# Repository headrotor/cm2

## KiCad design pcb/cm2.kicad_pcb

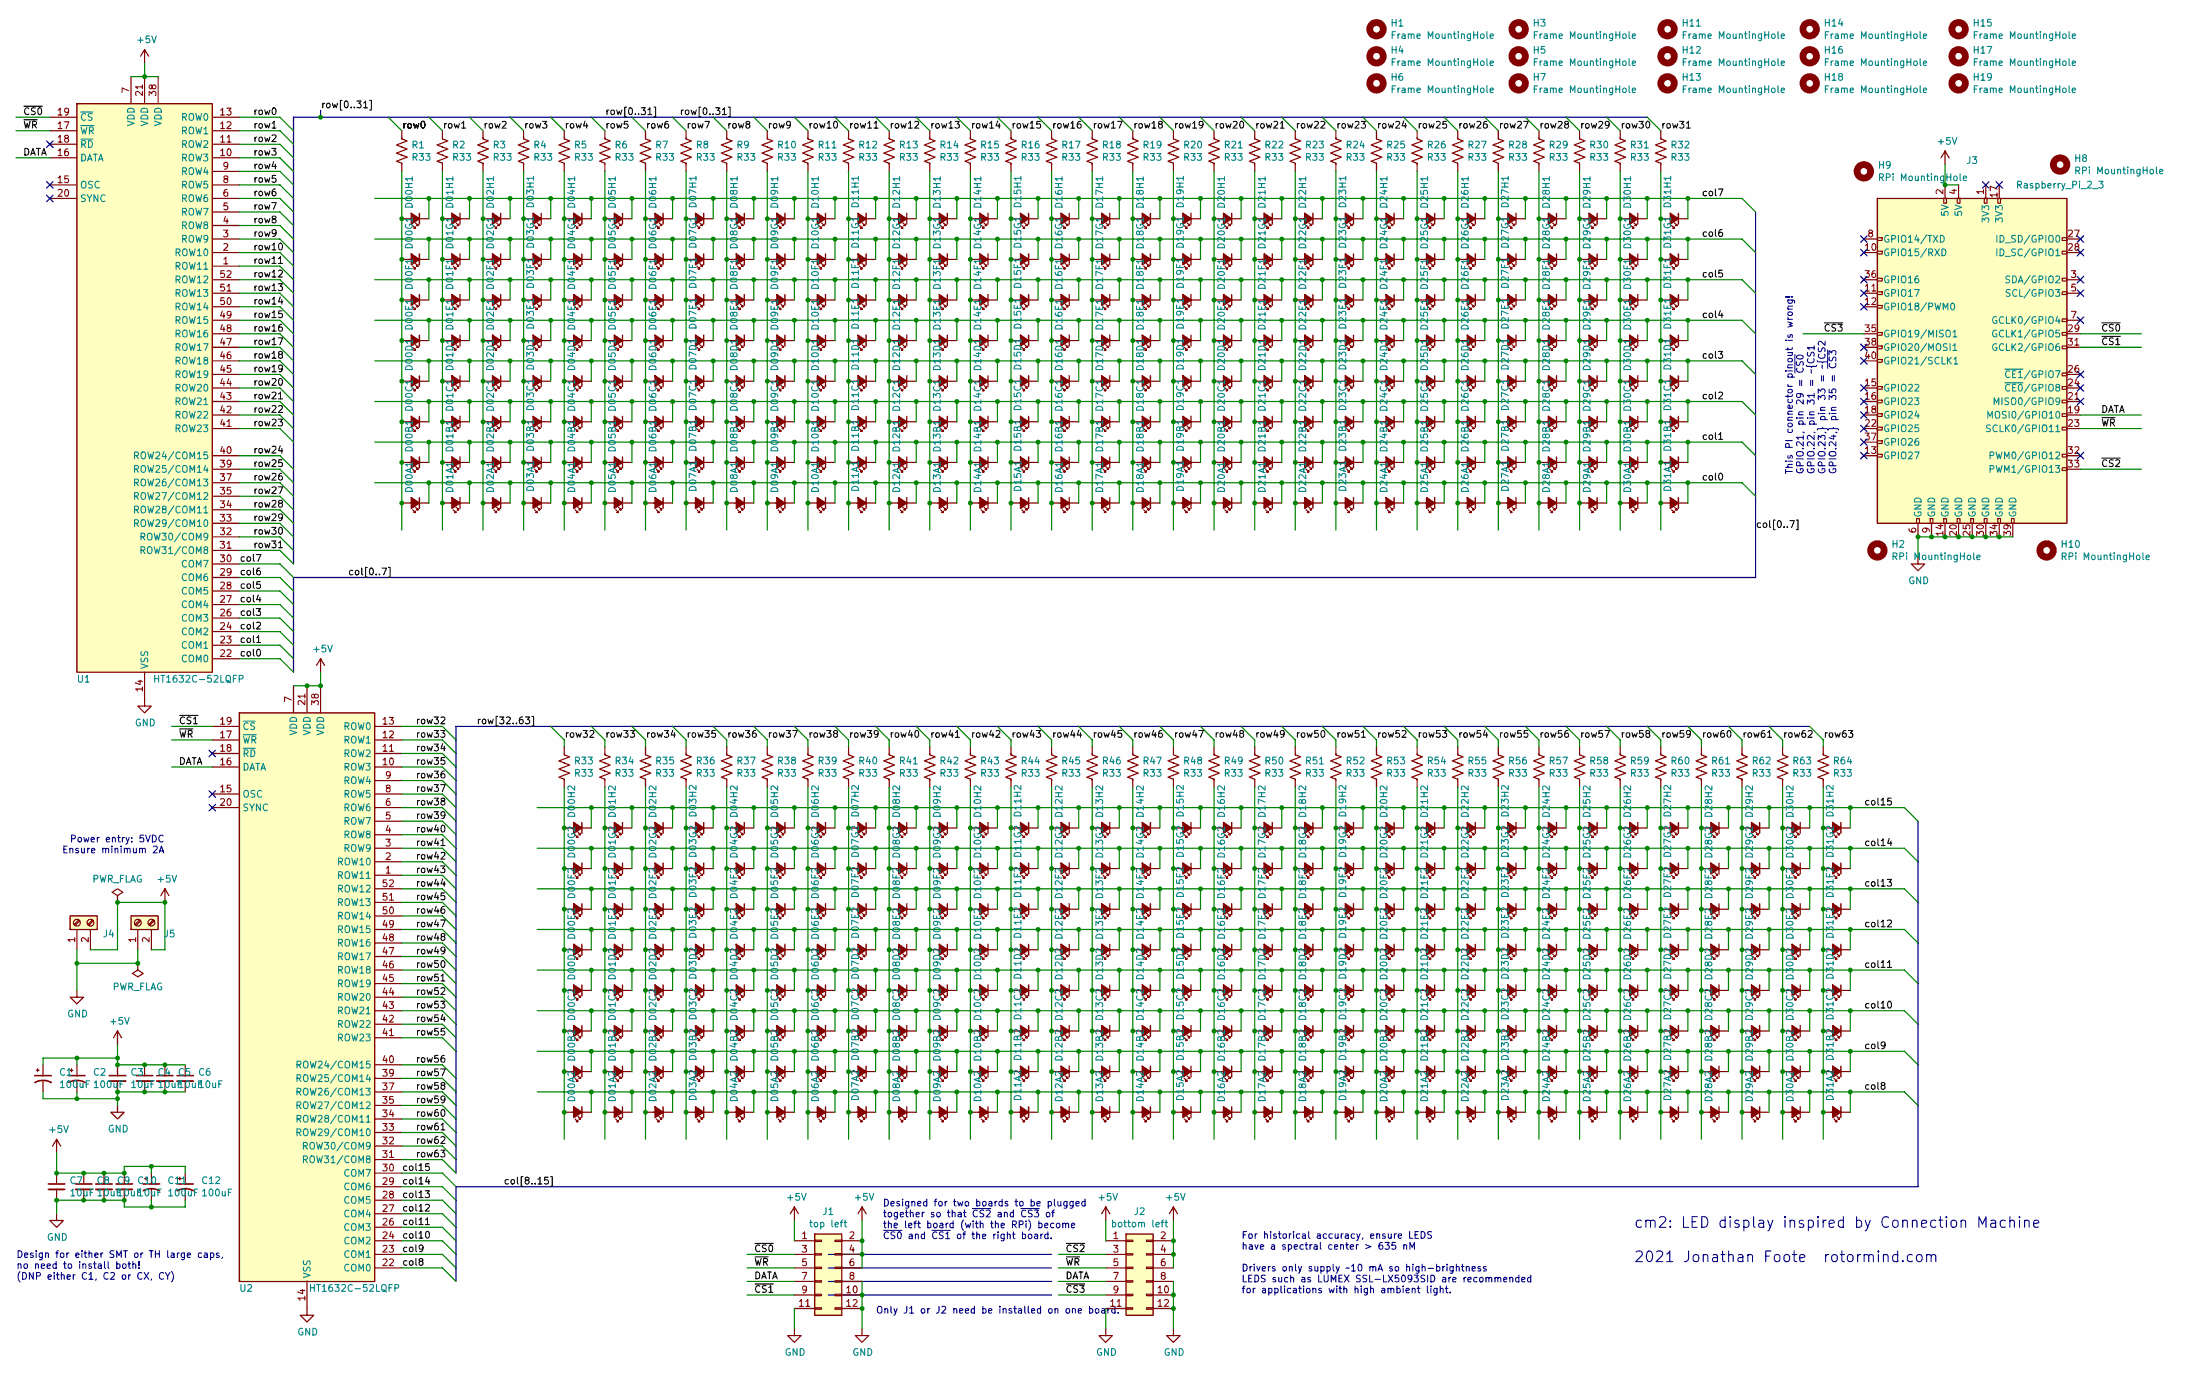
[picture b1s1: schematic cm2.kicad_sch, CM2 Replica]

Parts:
C1, C2: 100uF; CP_Radial_D6.3mm_P2.50mm
C3, C4, C5, C6, C7, C8, C9, C10: 10uF; C_1206_3216Metric_Pad1.33x1.80mm_HandSolder
C11, C12: 100uF; CP_Elec_6.3x7.7
D00A1, D00A2, D00B1, D00B2, D00C1, D00C2, D00D1, D00D2, D00E1, D00E2, D00F1, D00F2, D00G1, D00G2, D00H1, D00H2, D01A1, D01A2, D01B1, D01B2, D01C1, D01C2, D01D1, D01D2, D01E1, D01E2, D01F1, D01F2, D01G1, D01G2, D01H1, D01H2, D02A1, D02A2, D02B1, D02B2, D02C1, D02C2, D02D1, D02D2, D02E1, D02E2, D02F1, D02F2, D02G1, D02G2, D02H1, D02H2, D03A1, D03A2, D03B1, D03B2, D03C1, D03C2, D03D1, D03D2, D03E1, D03E2, D03F1, D03F2, D03G1, D03G2, D03H1, D03H2, D04A1, D04A2, D04B1, D04B2, D04C1, D04C2, D04D1, D04D2, D04E1, D04E2, D04F1, D04F2, D04G1, D04G2, D04H1, D04H2, D05A1, D05A2, D05B1, D05B2, D05C1, D05C2, D05D1, D05D2, D05E1, D05E2, D05F1, D05F2, D05G1, D05G2, D05H1, D05H2, D06A1, D06A2, D06B1, D06B2, D06C1, D06C2, D06D1, D06D2, D06E1, D06E2, D06F1, D06F2, D06G1, D06G2, D06H1, D06H2, D07A1, D07A2, D07B1, D07B2, D07C1, D07C2, D07D1, D07D2, D07E1, D07E2, D07F1, D07F2, D07G1, D07G2, D07H1, D07H2, D08A1, D08A2, D08B1, D08B2, D08C1, D08C2, D08D1, D08D2, D08E1, D08E2, D08F1, D08F2, D08G1, D08G2, D08H1, D08H2, D09A1, D09A2, D09B1, D09B2, D09C1, D09C2, D09D1, D09D2, D09E1, D09E2, D09F1, D09F2, D09G1, D09G2, D09H1, D09H2, D10A1, D10A2, D10B1, D10B2, D10C1, D10C2, D10D1, D10D2, D10E1, D10E2, D10F1, D10F2, D10G1, D10G2, D10H1, D10H2, D11A1, D11A2, D11B1, D11B2, D11C1, D11C2, D11D1, D11D2, D11E1, D11E2, D11F1, D11F2, D11G1, D11G2, D11H1, D11H2, D12A1, D12A2, D12B1, D12B2, D12C1, D12C2, D12D1, D12D2, D12E1, D12E2, D12F1, D12F2, D12G1, D12G2, D12H1, D12H2, D13A1, D13A2, D13B1, D13B2, D13C1, D13C2, D13D1, D13D2, D13E1, D13E2, D13F1, D13F2, D13G1, D13G2, D13H1, D13H2, D14A1, D14A2, D14B1, D14B2, D14C1, D14C2, D14D1, D14D2, D14E1, D14E2, D14F1, D14F2, D14G1, D14G2, D14H1, D14H2, D15A1, D15A2, D15B1, D15B2, D15C1, D15C2, D15D1, D15D2, D15E1, D15E2, D15F1, D15F2, D15G1, D15G2, D15H1, D15H2, D16A1, D16A2, D16B1, D16B2, D16C1, D16C2, D16D1, D16D2, D16E1, D16E2, D16F1, D16F2, D16G1, D16G2, D16H1, D16H2, D17A1, D17A2, D17B1, D17B2, D17C1, D17C2, D17D1, D17D2, D17E1, D17E2, D17F1, D17F2, D17G1, D17G2, D17H1, D17H2, D18A1, D18A2, D18B1, D18B2, D18C1, D18C2, D18D1, D18D2, D18E1, D18E2, D18F1, D18F2, D18G1, D18G2, D18H1, D18H2, D19A1, D19A2, D19B1, D19B2, D19C1, D19C2, D19D1, D19D2, D19E1, D19E2, D19F1, D19F2, D19G1, D19G2, D19H1, D19H2, D20A1, D20A2, D20B1, D20B2, D20C1, D20C2, D20D1, D20D2, D20E1, D20E2, D20F1, D20F2, D20G1, D20G2, D20H1, D20H2, D21A1, D21A2, D21B1, D21B2, D21C1, D21C2, D21D1, D21D2, D21E1, D21E2, D21F1, D21F2, D21G1, D21G2, D21H1, D21H2, D22A1, D22A2, D22B1, D22B2, D22C1, D22C2, D22D1, D22D2, D22E1, D22E2, D22F1, D22F2, D22G1, D22G2, D22H1, D22H2, D23A1, D23A2, D23B1, D23B2, D23C1, D23C2, D23D1, D23D2, D23E1, D23E2, D23F1, D23F2, D23G1, D23G2, D23H1, D23H2, D24A1, D24A2, D24B1, D24B2, D24C1, D24C2, D24D1, D24D2, D24E1, D24E2, D24F1, D24F2, D24G1, D24G2, D24H1, D24H2, D25A1, D25A2, D25B1, D25B2, D25C1, D25C2, D25D1, D25D2, D25E1, D25E2, D25F1, D25F2, D25G1, D25G2, D25H1, D25H2, D26A1, D26A2, D26B1, D26B2, D26C1, D26C2, D26D1, D26D2, D26E1, D26E2, D26F1, D26F2, D26G1, D26G2, D26H1, D26H2, D27A1, D27A2, D27B1, D27B2, D27C1, D27C2, D27D1, D27D2, D27E1, D27E2, D27F1, D27F2, D27G1, D27G2, D27H1, D27H2, D28A1, D28A2, D28B1, D28B2, D28C1, D28C2, D28D1, D28D2, D28E1, D28E2, D28F1, D28F2, D28G1, D28G2, D28H1, D28H2, D29A1, D29A2, D29B1, D29B2, D29C1, D29C2, D29D1, D29D2, D29E1, D29E2, D29F1, D29F2, D29G1, D29G2, D29H1, D29H2, D30A1, D30A2, D30B1, D30B2, D30C1, D30C2, D30D1, D30D2, D30E1, D30E2, D30F1, D30F2, D30G1, D30G2, D30H1, D30H2, D31A1, D31A2, D31B1, D31B2, D31C1, D31C2, D31D1, D31D2, D31E1, D31E2, D31F1, D31F2, D31G1, D31G2, D31H1, D31H2: LED_Small_ALT; LED_D5.0mm
H1, H3, H4, H5, H6, H7, H11, H12, H13, H14, H15, H16, H17, H18, H19: Frame MountingHole; MountingHole_3.2mm_M3
H2, H8, H9, H10: RPi MountingHole; MountingHole_2.5mm
J1: top left; PinHeader_2x06_P2.54mm_Horizontal
J2: bottom left; PinSocket_2x06_P2.54mm_Horizontal
J3: Raspberry_Pi_2_3; PinSocket_2x20_P2.54mm_Vertical
J4, J5: Screw_Terminal_01x02; TerminalBlock_bornier-2_P5.08mm
R1, R2, R3, R4, R5, R6, R7, R8, R9, R10, R11, R12, R13, R14, R15, R16, R17, R18, R19, R20, R21, R22, R23, R24, R25, R26, R27, R28, R29, R30, R31, R32, R33, R34, R35, R36, R37, R38, R39, R40, R41, R42, R43, R44, R45, R46, R47, R48, R49, R50, R51, R52, R53, R54, R55, R56, R57, R58, R59, R60, R61, R62, R63, R64: R33; R_0603_1608Metric_Pad0.98x0.95mm_HandSolder
U1, U2: HT1632C-52LQFP; LQFP-52_14x14mm_P1mm

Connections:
+5V: C1.1, C2.1, C3.1, C4.1, C5.1, C6.1, C7.1, C8.1, C9.1, C10.1, C11.1, C12.1, J1.1, J1.2, J1.4, J1.6, J2.1, J2.2, J2.4, J2.6, J3.2 (5V), J3.4 (5V), J4.2, J5.2, U1.7 (VDD), U1.21 (VDD), U1.38 (VDD), U2.7 (VDD), U2.21 (VDD), U2.38 (VDD); also elsewhere on the board
/DATA: J1.7, J2.7, J3.19 (MOSI0/GPIO10), U1.16 (DATA), U2.16 (DATA)
/col0: D00A1.1 (K), D01A1.1 (K), D02A1.1 (K), D03A1.1 (K), D04A1.1 (K), D05A1.1 (K), D06A1.1 (K), D07A1.1 (K), D08A1.1 (K), D09A1.1 (K), D10A1.1 (K), D11A1.1 (K), D12A1.1 (K), D13A1.1 (K), D14A1.1 (K), D15A1.1 (K), D16A1.1 (K), D17A1.1 (K), D18A1.1 (K), D19A1.1 (K), D20A1.1 (K), D21A1.1 (K), D22A1.1 (K), D23A1.1 (K), D24A1.1 (K), D25A1.1 (K), D26A1.1 (K), D27A1.1 (K), D28A1.1 (K), D29A1.1 (K), D30A1.1 (K), D31A1.1 (K), U1.22 (COM0)
/col1: D00B1.1 (K), D01B1.1 (K), D02B1.1 (K), D03B1.1 (K), D04B1.1 (K), D05B1.1 (K), D06B1.1 (K), D07B1.1 (K), D08B1.1 (K), D09B1.1 (K), D10B1.1 (K), D11B1.1 (K), D12B1.1 (K), D13B1.1 (K), D14B1.1 (K), D15B1.1 (K), D16B1.1 (K), D17B1.1 (K), D18B1.1 (K), D19B1.1 (K), D20B1.1 (K), D21B1.1 (K), D22B1.1 (K), D23B1.1 (K), D24B1.1 (K), D25B1.1 (K), D26B1.1 (K), D27B1.1 (K), D28B1.1 (K), D29B1.1 (K), D30B1.1 (K), D31B1.1 (K), U1.23 (COM1)
/col2: D00C1.1 (K), D01C1.1 (K), D02C1.1 (K), D03C1.1 (K), D04C1.1 (K), D05C1.1 (K), D06C1.1 (K), D07C1.1 (K), D08C1.1 (K), D09C1.1 (K), D10C1.1 (K), D11C1.1 (K), D12C1.1 (K), D13C1.1 (K), D14C1.1 (K), D15C1.1 (K), D16C1.1 (K), D17C1.1 (K), D18C1.1 (K), D19C1.1 (K), D20C1.1 (K), D21C1.1 (K), D22C1.1 (K), D23C1.1 (K), D24C1.1 (K), D25C1.1 (K), D26C1.1 (K), D27C1.1 (K), D28C1.1 (K), D29C1.1 (K), D30C1.1 (K), D31C1.1 (K), U1.24 (COM2)
/col3: D00D1.1 (K), D01D1.1 (K), D02D1.1 (K), D03D1.1 (K), D04D1.1 (K), D05D1.1 (K), D06D1.1 (K), D07D1.1 (K), D08D1.1 (K), D09D1.1 (K), D10D1.1 (K), D11D1.1 (K), D12D1.1 (K), D13D1.1 (K), D14D1.1 (K), D15D1.1 (K), D16D1.1 (K), D17D1.1 (K), D18D1.1 (K), D19D1.1 (K), D20D1.1 (K), D21D1.1 (K), D22D1.1 (K), D23D1.1 (K), D24D1.1 (K), D25D1.1 (K), D26D1.1 (K), D27D1.1 (K), D28D1.1 (K), D29D1.1 (K), D30D1.1 (K), D31D1.1 (K), U1.26 (COM3)
/col4: D00E1.1 (K), D01E1.1 (K), D02E1.1 (K), D03E1.1 (K), D04E1.1 (K), D05E1.1 (K), D06E1.1 (K), D07E1.1 (K), D08E1.1 (K), D09E1.1 (K), D10E1.1 (K), D11E1.1 (K), D12E1.1 (K), D13E1.1 (K), D14E1.1 (K), D15E1.1 (K), D16E1.1 (K), D17E1.1 (K), D18E1.1 (K), D19E1.1 (K), D20E1.1 (K), D21E1.1 (K), D22E1.1 (K), D23E1.1 (K), D24E1.1 (K), D25E1.1 (K), D26E1.1 (K), D27E1.1 (K), D28E1.1 (K), D29E1.1 (K), D30E1.1 (K), D31E1.1 (K), U1.27 (COM4)
/col5: D00F1.1 (K), D01F1.1 (K), D02F1.1 (K), D03F1.1 (K), D04F1.1 (K), D05F1.1 (K), D06F1.1 (K), D07F1.1 (K), D08F1.1 (K), D09F1.1 (K), D10F1.1 (K), D11F1.1 (K), D12F1.1 (K), D13F1.1 (K), D14F1.1 (K), D15F1.1 (K), D16F1.1 (K), D17F1.1 (K), D18F1.1 (K), D19F1.1 (K), D20F1.1 (K), D21F1.1 (K), D22F1.1 (K), D23F1.1 (K), D24F1.1 (K), D25F1.1 (K), D26F1.1 (K), D27F1.1 (K), D28F1.1 (K), D29F1.1 (K), D30F1.1 (K), D31F1.1 (K), U1.28 (COM5)
/col6: D00G1.1 (K), D01G1.1 (K), D02G1.1 (K), D03G1.1 (K), D04G1.1 (K), D05G1.1 (K), D06G1.1 (K), D07G1.1 (K), D08G1.1 (K), D09G1.1 (K), D10G1.1 (K), D11G1.1 (K), D12G1.1 (K), D13G1.1 (K), D14G1.1 (K), D15G1.1 (K), D16G1.1 (K), D17G1.1 (K), D18G1.1 (K), D19G1.1 (K), D20G1.1 (K), D21G1.1 (K), D22G1.1 (K), D23G1.1 (K), D24G1.1 (K), D25G1.1 (K), D26G1.1 (K), D27G1.1 (K), D28G1.1 (K), D29G1.1 (K), D30G1.1 (K), D31G1.1 (K), U1.29 (COM6)
/col7: D00H1.1 (K), D01H1.1 (K), D02H1.1 (K), D03H1.1 (K), D04H1.1 (K), D05H1.1 (K), D06H1.1 (K), D07H1.1 (K), D08H1.1 (K), D09H1.1 (K), D10H1.1 (K), D11H1.1 (K), D12H1.1 (K), D13H1.1 (K), D14H1.1 (K), D15H1.1 (K), D16H1.1 (K), D17H1.1 (K), D18H1.1 (K), D19H1.1 (K), D20H1.1 (K), D21H1.1 (K), D22H1.1 (K), D23H1.1 (K), D24H1.1 (K), D25H1.1 (K), D26H1.1 (K), D27H1.1 (K), D28H1.1 (K), D29H1.1 (K), D30H1.1 (K), D31H1.1 (K), U1.30 (COM7)
/col8: D00A2.1 (K), D01A2.1 (K), D02A2.1 (K), D03A2.1 (K), D04A2.1 (K), D05A2.1 (K), D06A2.1 (K), D07A2.1 (K), D08A2.1 (K), D09A2.1 (K), D10A2.1 (K), D11A2.1 (K), D12A2.1 (K), D13A2.1 (K), D14A2.1 (K), D15A2.1 (K), D16A2.1 (K), D17A2.1 (K), D18A2.1 (K), D19A2.1 (K), D20A2.1 (K), D21A2.1 (K), D22A2.1 (K), D23A2.1 (K), D24A2.1 (K), D25A2.1 (K), D26A2.1 (K), D27A2.1 (K), D28A2.1 (K), D29A2.1 (K), D30A2.1 (K), D31A2.1 (K), U2.22 (COM0)
/col9: D00B2.1 (K), D01B2.1 (K), D02B2.1 (K), D03B2.1 (K), D04B2.1 (K), D05B2.1 (K), D06B2.1 (K), D07B2.1 (K), D08B2.1 (K), D09B2.1 (K), D10B2.1 (K), D11B2.1 (K), D12B2.1 (K), D13B2.1 (K), D14B2.1 (K), D15B2.1 (K), D16B2.1 (K), D17B2.1 (K), D18B2.1 (K), D19B2.1 (K), D20B2.1 (K), D21B2.1 (K), D22B2.1 (K), D23B2.1 (K), D24B2.1 (K), D25B2.1 (K), D26B2.1 (K), D27B2.1 (K), D28B2.1 (K), D29B2.1 (K), D30B2.1 (K), D31B2.1 (K), U2.23 (COM1)
/col10: D00C2.1 (K), D01C2.1 (K), D02C2.1 (K), D03C2.1 (K), D04C2.1 (K), D05C2.1 (K), D06C2.1 (K), D07C2.1 (K), D08C2.1 (K), D09C2.1 (K), D10C2.1 (K), D11C2.1 (K), D12C2.1 (K), D13C2.1 (K), D14C2.1 (K), D15C2.1 (K), D16C2.1 (K), D17C2.1 (K), D18C2.1 (K), D19C2.1 (K), D20C2.1 (K), D21C2.1 (K), D22C2.1 (K), D23C2.1 (K), D24C2.1 (K), D25C2.1 (K), D26C2.1 (K), D27C2.1 (K), D28C2.1 (K), D29C2.1 (K), D30C2.1 (K), D31C2.1 (K), U2.24 (COM2)
/col11: D00D2.1 (K), D01D2.1 (K), D02D2.1 (K), D03D2.1 (K), D04D2.1 (K), D05D2.1 (K), D06D2.1 (K), D07D2.1 (K), D08D2.1 (K), D09D2.1 (K), D10D2.1 (K), D11D2.1 (K), D12D2.1 (K), D13D2.1 (K), D14D2.1 (K), D15D2.1 (K), D16D2.1 (K), D17D2.1 (K), D18D2.1 (K), D19D2.1 (K), D20D2.1 (K), D21D2.1 (K), D22D2.1 (K), D23D2.1 (K), D24D2.1 (K), D25D2.1 (K), D26D2.1 (K), D27D2.1 (K), D28D2.1 (K), D29D2.1 (K), D30D2.1 (K), D31D2.1 (K), U2.26 (COM3)
/col12: D00E2.1 (K), D01E2.1 (K), D02E2.1 (K), D03E2.1 (K), D04E2.1 (K), D05E2.1 (K), D06E2.1 (K), D07E2.1 (K), D08E2.1 (K), D09E2.1 (K), D10E2.1 (K), D11E2.1 (K), D12E2.1 (K), D13E2.1 (K), D14E2.1 (K), D15E2.1 (K), D16E2.1 (K), D17E2.1 (K), D18E2.1 (K), D19E2.1 (K), D20E2.1 (K), D21E2.1 (K), D22E2.1 (K), D23E2.1 (K), D24E2.1 (K), D25E2.1 (K), D26E2.1 (K), D27E2.1 (K), D28E2.1 (K), D29E2.1 (K), D30E2.1 (K), D31E2.1 (K), U2.27 (COM4)
/col13: D00F2.1 (K), D01F2.1 (K), D02F2.1 (K), D03F2.1 (K), D04F2.1 (K), D05F2.1 (K), D06F2.1 (K), D07F2.1 (K), D08F2.1 (K), D09F2.1 (K), D10F2.1 (K), D11F2.1 (K), D12F2.1 (K), D13F2.1 (K), D14F2.1 (K), D15F2.1 (K), D16F2.1 (K), D17F2.1 (K), D18F2.1 (K), D19F2.1 (K), D20F2.1 (K), D21F2.1 (K), D22F2.1 (K), D23F2.1 (K), D24F2.1 (K), D25F2.1 (K), D26F2.1 (K), D27F2.1 (K), D28F2.1 (K), D29F2.1 (K), D30F2.1 (K), D31F2.1 (K), U2.28 (COM5)
/col14: D00G2.1 (K), D01G2.1 (K), D02G2.1 (K), D03G2.1 (K), D04G2.1 (K), D05G2.1 (K), D06G2.1 (K), D07G2.1 (K), D08G2.1 (K), D09G2.1 (K), D10G2.1 (K), D11G2.1 (K), D12G2.1 (K), D13G2.1 (K), D14G2.1 (K), D15G2.1 (K), D16G2.1 (K), D17G2.1 (K), D18G2.1 (K), D19G2.1 (K), D20G2.1 (K), D21G2.1 (K), D22G2.1 (K), D23G2.1 (K), D24G2.1 (K), D25G2.1 (K), D26G2.1 (K), D27G2.1 (K), D28G2.1 (K), D29G2.1 (K), D30G2.1 (K), D31G2.1 (K), U2.29 (COM6)
/col15: D00H2.1 (K), D01H2.1 (K), D02H2.1 (K), D03H2.1 (K), D04H2.1 (K), D05H2.1 (K), D06H2.1 (K), D07H2.1 (K), D08H2.1 (K), D09H2.1 (K), D10H2.1 (K), D11H2.1 (K), D12H2.1 (K), D13H2.1 (K), D14H2.1 (K), D15H2.1 (K), D16H2.1 (K), D17H2.1 (K), D18H2.1 (K), D19H2.1 (K), D20H2.1 (K), D21H2.1 (K), D22H2.1 (K), D23H2.1 (K), D24H2.1 (K), D25H2.1 (K), D26H2.1 (K), D27H2.1 (K), D28H2.1 (K), D29H2.1 (K), D30H2.1 (K), D31H2.1 (K), U2.30 (COM7)
/row0: R1.1, U1.13 (ROW0)
/row1: R2.1, U1.12 (ROW1)
/row2: R3.1, U1.11 (ROW2)
/row3: R4.1, U1.10 (ROW3)
/row4: R5.1, U1.9 (ROW4)
/row5: R6.1, U1.8 (ROW5)
/row6: R7.1, U1.6 (ROW6)
/row7: R8.1, U1.5 (ROW7)
/row8: R9.1, U1.4 (ROW8)
/row9: R10.1, U1.3 (ROW9)
/row10: R11.1, U1.2 (ROW10)
/row11: R12.1, U1.1 (ROW11)
/row12: R13.1, U1.52 (ROW12)
/row13: R14.1, U1.51 (ROW13)
/row14: R15.1, U1.50 (ROW14)
/row15: R16.1, U1.49 (ROW15)
/row16: R17.1, U1.48 (ROW16)
/row17: R18.1, U1.47 (ROW17)
/row18: R19.1, U1.46 (ROW18)
/row19: R20.1, U1.45 (ROW19)
/row20: R21.1, U1.44 (ROW20)
/row21: R22.1, U1.43 (ROW21)
/row22: R23.1, U1.42 (ROW22)
/row23: R24.1, U1.41 (ROW23)
/row24: R25.1, U1.40 (ROW24/COM15)
/row25: R26.1, U1.39 (ROW25/COM14)
/row26: R27.1, U1.37 (ROW26/COM13)
/row27: R28.1, U1.35 (ROW27/COM12)
/row28: R29.1, U1.34 (ROW28/COM11)
/row29: R30.1, U1.33 (ROW29/COM10)
/row30: R31.1, U1.32 (ROW30/COM9)
/row31: R32.1, U1.31 (ROW31/COM8)
/row32: R33.1, U2.13 (ROW0)
/row33: R34.1, U2.12 (ROW1)
/row34: R35.1, U2.11 (ROW2)
/row35: R36.1, U2.10 (ROW3)
/row36: R37.1, U2.9 (ROW4)
/row37: R38.1, U2.8 (ROW5)
/row38: R39.1, U2.6 (ROW6)
/row39: R40.1, U2.5 (ROW7)
/row40: R41.1, U2.4 (ROW8)
/row41: R42.1, U2.3 (ROW9)
/row42: R43.1, U2.2 (ROW10)
/row43: R44.1, U2.1 (ROW11)
/row44: R45.1, U2.52 (ROW12)
/row45: R46.1, U2.51 (ROW13)
/row46: R47.1, U2.50 (ROW14)
/row47: R48.1, U2.49 (ROW15)
/row48: R49.1, U2.48 (ROW16)
/row49: R50.1, U2.47 (ROW17)
/row50: R51.1, U2.46 (ROW18)
/row51: R52.1, U2.45 (ROW19)
/row52: R53.1, U2.44 (ROW20)
/row53: R54.1, U2.43 (ROW21)
/row54: R55.1, U2.42 (ROW22)
/row55: R56.1, U2.41 (ROW23)
/row56: R57.1, U2.40 (ROW24/COM15)
/row57: R58.1, U2.39 (ROW25/COM14)
/row58: R59.1, U2.37 (ROW26/COM13)
/row59: R60.1, U2.35 (ROW27/COM12)
/row60: R61.1, U2.34 (ROW28/COM11)
/row61: R62.1, U2.33 (ROW29/COM10)
/row62: R63.1, U2.32 (ROW30/COM9)
/row63: R64.1, U2.31 (ROW31/COM8)
/~CS0: J1.3, J3.29 (GCLK1/GPIO5), U1.19 (~CS)
/~CS1: J1.9, J3.31 (GCLK2/GPIO6), U2.19 (~CS)
/~CS2: J2.3, J3.33 (PWM1/GPIO13)
/~CS3: J2.9, J3.35 (GPIO19/MISO1)
/~WR: J1.5, J2.5, J3.23 (SCLK0/GPIO11), U1.17 (~WR), U2.17 (~WR)
GND: C1.2, C2.2, C3.2, C4.2, C5.2, C6.2, C7.2, C8.2, C9.2, C10.2, C11.2, C12.2, J1.8, J1.10, J1.11, J1.12, J2.8, J2.10, J2.11, J2.12, J3.6 (GND), J3.9 (GND), J3.14 (GND), J3.20 (GND), J3.25 (GND), J3.30 (GND), J3.34 (GND), J3.39 (GND), J4.1, J5.1, U1.14 (VSS), U1.25 (VSS), U1.36 (VSS), U2.14 (VSS), U2.25 (VSS), U2.36 (VSS); also elsewhere on the board
unnamed: D00A1.2 (A), D00B1.2 (A), D00C1.2 (A), D00D1.2 (A), D00E1.2 (A), D00F1.2 (A), D00G1.2 (A), D00H1.2 (A), R1.2
unnamed: D00A2.2 (A), D00B2.2 (A), D00C2.2 (A), D00D2.2 (A), D00E2.2 (A), D00F2.2 (A), D00G2.2 (A), D00H2.2 (A), R33.2
unnamed: D01A1.2 (A), D01B1.2 (A), D01C1.2 (A), D01D1.2 (A), D01E1.2 (A), D01F1.2 (A), D01G1.2 (A), D01H1.2 (A), R2.2
unnamed: D01A2.2 (A), D01B2.2 (A), D01C2.2 (A), D01D2.2 (A), D01E2.2 (A), D01F2.2 (A), D01G2.2 (A), D01H2.2 (A), R34.2
unnamed: D02A1.2 (A), D02B1.2 (A), D02C1.2 (A), D02D1.2 (A), D02E1.2 (A), D02F1.2 (A), D02G1.2 (A), D02H1.2 (A), R3.2
unnamed: D02A2.2 (A), D02B2.2 (A), D02C2.2 (A), D02D2.2 (A), D02E2.2 (A), D02F2.2 (A), D02G2.2 (A), D02H2.2 (A), R35.2
unnamed: D03A1.2 (A), D03B1.2 (A), D03C1.2 (A), D03D1.2 (A), D03E1.2 (A), D03F1.2 (A), D03G1.2 (A), D03H1.2 (A), R4.2
unnamed: D03A2.2 (A), D03B2.2 (A), D03C2.2 (A), D03D2.2 (A), D03E2.2 (A), D03F2.2 (A), D03G2.2 (A), D03H2.2 (A), R36.2
unnamed: D04A1.2 (A), D04B1.2 (A), D04C1.2 (A), D04D1.2 (A), D04E1.2 (A), D04F1.2 (A), D04G1.2 (A), D04H1.2 (A), R5.2
unnamed: D05A1.2 (A), D05B1.2 (A), D05C1.2 (A), D05D1.2 (A), D05E1.2 (A), D05F1.2 (A), D05G1.2 (A), D05H1.2 (A), R6.2
unnamed: D06A1.2 (A), D06B1.2 (A), D06C1.2 (A), D06D1.2 (A), D06E1.2 (A), D06F1.2 (A), D06G1.2 (A), D06H1.2 (A), R7.2
unnamed: D07A1.2 (A), D07B1.2 (A), D07C1.2 (A), D07D1.2 (A), D07E1.2 (A), D07F1.2 (A), D07G1.2 (A), D07H1.2 (A), R8.2
unnamed: D08A1.2 (A), D08B1.2 (A), D08C1.2 (A), D08D1.2 (A), D08E1.2 (A), D08F1.2 (A), D08G1.2 (A), D08H1.2 (A), R9.2
unnamed: D08A2.2 (A), D08B2.2 (A), D08C2.2 (A), D08D2.2 (A), D08E2.2 (A), D08F2.2 (A), D08G2.2 (A), D08H2.2 (A), R41.2
unnamed: D09A2.2 (A), D09B2.2 (A), D09C2.2 (A), D09D2.2 (A), D09E2.2 (A), D09F2.2 (A), D09G2.2 (A), D09H2.2 (A), R42.2
unnamed: D09A1.2 (A), D09B1.2 (A), D09C1.2 (A), D09D1.2 (A), D09E1.2 (A), D09F1.2 (A), D09G1.2 (A), D09H1.2 (A), R10.2
unnamed: D10A2.2 (A), D10B2.2 (A), D10C2.2 (A), D10D2.2 (A), D10E2.2 (A), D10F2.2 (A), D10G2.2 (A), D10H2.2 (A), R43.2
unnamed: D10A1.2 (A), D10B1.2 (A), D10C1.2 (A), D10D1.2 (A), D10E1.2 (A), D10F1.2 (A), D10G1.2 (A), D10H1.2 (A), R11.2
unnamed: D11A2.2 (A), D11B2.2 (A), D11C2.2 (A), D11D2.2 (A), D11E2.2 (A), D11F2.2 (A), D11G2.2 (A), D11H2.2 (A), R44.2
unnamed: D11A1.2 (A), D11B1.2 (A), D11C1.2 (A), D11D1.2 (A), D11E1.2 (A), D11F1.2 (A), D11G1.2 (A), D11H1.2 (A), R12.2
unnamed: D12A1.2 (A), D12B1.2 (A), D12C1.2 (A), D12D1.2 (A), D12E1.2 (A), D12F1.2 (A), D12G1.2 (A), D12H1.2 (A), R13.2
unnamed: D12A2.2 (A), D12B2.2 (A), D12C2.2 (A), D12D2.2 (A), D12E2.2 (A), D12F2.2 (A), D12G2.2 (A), D12H2.2 (A), R45.2
unnamed: D13A1.2 (A), D13B1.2 (A), D13C1.2 (A), D13D1.2 (A), D13E1.2 (A), D13F1.2 (A), D13G1.2 (A), D13H1.2 (A), R14.2
unnamed: D14A1.2 (A), D14B1.2 (A), D14C1.2 (A), D14D1.2 (A), D14E1.2 (A), D14F1.2 (A), D14G1.2 (A), D14H1.2 (A), R15.2
unnamed: D14A2.2 (A), D14B2.2 (A), D14C2.2 (A), D14D2.2 (A), D14E2.2 (A), D14F2.2 (A), D14G2.2 (A), D14H2.2 (A), R47.2
unnamed: D15A2.2 (A), D15B2.2 (A), D15C2.2 (A), D15D2.2 (A), D15E2.2 (A), D15F2.2 (A), D15G2.2 (A), D15H2.2 (A), R48.2
unnamed: D15A1.2 (A), D15B1.2 (A), D15C1.2 (A), D15D1.2 (A), D15E1.2 (A), D15F1.2 (A), D15G1.2 (A), D15H1.2 (A), R16.2
unnamed: D16A1.2 (A), D16B1.2 (A), D16C1.2 (A), D16D1.2 (A), D16E1.2 (A), D16F1.2 (A), D16G1.2 (A), D16H1.2 (A), R17.2
unnamed: D16A2.2 (A), D16B2.2 (A), D16C2.2 (A), D16D2.2 (A), D16E2.2 (A), D16F2.2 (A), D16G2.2 (A), D16H2.2 (A), R49.2
unnamed: D17A1.2 (A), D17B1.2 (A), D17C1.2 (A), D17D1.2 (A), D17E1.2 (A), D17F1.2 (A), D17G1.2 (A), D17H1.2 (A), R18.2
unnamed: D18A1.2 (A), D18B1.2 (A), D18C1.2 (A), D18D1.2 (A), D18E1.2 (A), D18F1.2 (A), D18G1.2 (A), D18H1.2 (A), R19.2
unnamed: D18A2.2 (A), D18B2.2 (A), D18C2.2 (A), D18D2.2 (A), D18E2.2 (A), D18F2.2 (A), D18G2.2 (A), D18H2.2 (A), R51.2
unnamed: D19A1.2 (A), D19B1.2 (A), D19C1.2 (A), D19D1.2 (A), D19E1.2 (A), D19F1.2 (A), D19G1.2 (A), D19H1.2 (A), R20.2
unnamed: D19A2.2 (A), D19B2.2 (A), D19C2.2 (A), D19D2.2 (A), D19E2.2 (A), D19F2.2 (A), D19G2.2 (A), D19H2.2 (A), R52.2
unnamed: D20A2.2 (A), D20B2.2 (A), D20C2.2 (A), D20D2.2 (A), D20E2.2 (A), D20F2.2 (A), D20G2.2 (A), D20H2.2 (A), R53.2
unnamed: D20A1.2 (A), D20B1.2 (A), D20C1.2 (A), D20D1.2 (A), D20E1.2 (A), D20F1.2 (A), D20G1.2 (A), D20H1.2 (A), R21.2
unnamed: D21A2.2 (A), D21B2.2 (A), D21C2.2 (A), D21D2.2 (A), D21E2.2 (A), D21F2.2 (A), D21G2.2 (A), D21H2.2 (A), R54.2
unnamed: D22A1.2 (A), D22B1.2 (A), D22C1.2 (A), D22D1.2 (A), D22E1.2 (A), D22F1.2 (A), D22G1.2 (A), D22H1.2 (A), R23.2
unnamed: D22A2.2 (A), D22B2.2 (A), D22C2.2 (A), D22D2.2 (A), D22E2.2 (A), D22F2.2 (A), D22G2.2 (A), D22H2.2 (A), R55.2
unnamed: D23A2.2 (A), D23B2.2 (A), D23C2.2 (A), D23D2.2 (A), D23E2.2 (A), D23F2.2 (A), D23G2.2 (A), D23H2.2 (A), R56.2
unnamed: D25A2.2 (A), D25B2.2 (A), D25C2.2 (A), D25D2.2 (A), D25E2.2 (A), D25F2.2 (A), D25G2.2 (A), D25H2.2 (A), R58.2
unnamed: D26A1.2 (A), D26B1.2 (A), D26C1.2 (A), D26D1.2 (A), D26E1.2 (A), D26F1.2 (A), D26G1.2 (A), D26H1.2 (A), R27.2
unnamed: D27A1.2 (A), D27B1.2 (A), D27C1.2 (A), D27D1.2 (A), D27E1.2 (A), D27F1.2 (A), D27G1.2 (A), D27H1.2 (A), R28.2
unnamed: D27A2.2 (A), D27B2.2 (A), D27C2.2 (A), D27D2.2 (A), D27E2.2 (A), D27F2.2 (A), D27G2.2 (A), D27H2.2 (A), R60.2
unnamed: D28A1.2 (A), D28B1.2 (A), D28C1.2 (A), D28D1.2 (A), D28E1.2 (A), D28F1.2 (A), D28G1.2 (A), D28H1.2 (A), R29.2
unnamed: D28A2.2 (A), D28B2.2 (A), D28C2.2 (A), D28D2.2 (A), D28E2.2 (A), D28F2.2 (A), D28G2.2 (A), D28H2.2 (A), R61.2
unnamed: D29A1.2 (A), D29B1.2 (A), D29C1.2 (A), D29D1.2 (A), D29E1.2 (A), D29F1.2 (A), D29G1.2 (A), D29H1.2 (A), R30.2
unnamed: D29A2.2 (A), D29B2.2 (A), D29C2.2 (A), D29D2.2 (A), D29E2.2 (A), D29F2.2 (A), D29G2.2 (A), D29H2.2 (A), R62.2
unnamed: D30A1.2 (A), D30B1.2 (A), D30C1.2 (A), D30D1.2 (A), D30E1.2 (A), D30F1.2 (A), D30G1.2 (A), D30H1.2 (A), R31.2
unnamed: D31A1.2 (A), D31B1.2 (A), D31C1.2 (A), D31D1.2 (A), D31E1.2 (A), D31F1.2 (A), D31G1.2 (A), D31H1.2 (A), R32.2
unnamed: D21A1.2 (A), D21B1.2 (A), D21C1.2 (A), D21D1.2 (A), D21E1.2 (A), D21F1.2 (A), D21G1.2 (A), D21H1.2 (A), R22.2
unnamed: D23A1.2 (A), D23B1.2 (A), D23C1.2 (A), D23D1.2 (A), D23E1.2 (A), D23F1.2 (A), D23G1.2 (A), D23H1.2 (A), R24.2
unnamed: D24A1.2 (A), D24B1.2 (A), D24C1.2 (A), D24D1.2 (A), D24E1.2 (A), D24F1.2 (A), D24G1.2 (A), D24H1.2 (A), R25.2
unnamed: D25A1.2 (A), D25B1.2 (A), D25C1.2 (A), D25D1.2 (A), D25E1.2 (A), D25F1.2 (A), D25G1.2 (A), D25H1.2 (A), R26.2
unnamed: D04A2.2 (A), D04B2.2 (A), D04C2.2 (A), D04D2.2 (A), D04E2.2 (A), D04F2.2 (A), D04G2.2 (A), D04H2.2 (A), R37.2
unnamed: D05A2.2 (A), D05B2.2 (A), D05C2.2 (A), D05D2.2 (A), D05E2.2 (A), D05F2.2 (A), D05G2.2 (A), D05H2.2 (A), R38.2
unnamed: D06A2.2 (A), D06B2.2 (A), D06C2.2 (A), D06D2.2 (A), D06E2.2 (A), D06F2.2 (A), D06G2.2 (A), D06H2.2 (A), R39.2
unnamed: D07A2.2 (A), D07B2.2 (A), D07C2.2 (A), D07D2.2 (A), D07E2.2 (A), D07F2.2 (A), D07G2.2 (A), D07H2.2 (A), R40.2
unnamed: D13A2.2 (A), D13B2.2 (A), D13C2.2 (A), D13D2.2 (A), D13E2.2 (A), D13F2.2 (A), D13G2.2 (A), D13H2.2 (A), R46.2
unnamed: D17A2.2 (A), D17B2.2 (A), D17C2.2 (A), D17D2.2 (A), D17E2.2 (A), D17F2.2 (A), D17G2.2 (A), D17H2.2 (A), R50.2
unnamed: D24A2.2 (A), D24B2.2 (A), D24C2.2 (A), D24D2.2 (A), D24E2.2 (A), D24F2.2 (A), D24G2.2 (A), D24H2.2 (A), R57.2
unnamed: D26A2.2 (A), D26B2.2 (A), D26C2.2 (A), D26D2.2 (A), D26E2.2 (A), D26F2.2 (A), D26G2.2 (A), D26H2.2 (A), R59.2
unnamed: D30A2.2 (A), D30B2.2 (A), D30C2.2 (A), D30D2.2 (A), D30E2.2 (A), D30F2.2 (A), D30G2.2 (A), D30H2.2 (A), R63.2
unnamed: D31A2.2 (A), D31B2.2 (A), D31C2.2 (A), D31D2.2 (A), D31E2.2 (A), D31F2.2 (A), D31G2.2 (A), D31H2.2 (A), R64.2

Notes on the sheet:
For historical accuracy, ensure LEDS have a spectral center > 635 nM Drivers only supply ~10 mA so high-brightness LEDS such as LUMEX SSL-LX5093SID are recommended for applications with high ambient light.
Designed for two boards to be plugged together so that ~{CS2} and ~{CS3} of the left board (with the RPi) become ~{CS0} and ~{CS1} of the right board.
Power entry: 5VDC Ensure minimum 2A
cm2: LED display inspired by Connection Machine 2021 Jonathan Foote rotormind.com
This PI connector pinout is wrong! GPIO.21, pin 29 = ~{CS0} GPIO.22, pin 31 = ~{CS1 GPIO.23,} pin 33 = ~{CS2 GPIO.24,} pin 35 = ~{CS3}
Only J1 or J2 need be installed on one board.
Design for either SMT or TH large caps, no need to install both! (DNP either C1, C2 or CX, CY)

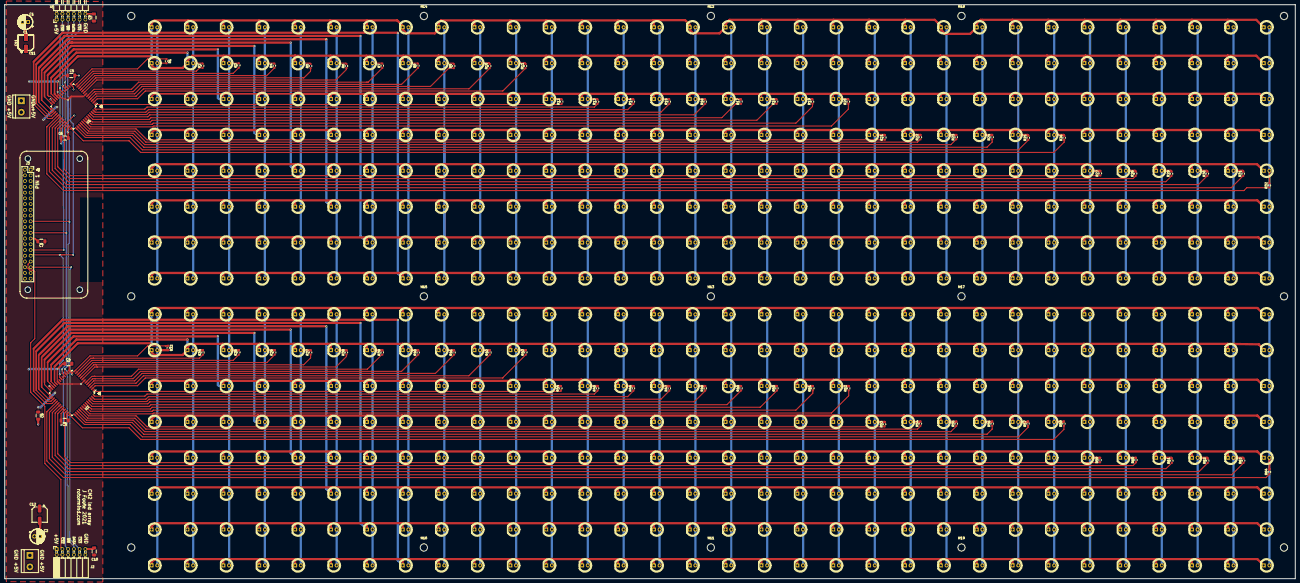
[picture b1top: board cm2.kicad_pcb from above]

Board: 2 copper layers, 571.1 x 254.0 mm, 618 parts (0 on the bottom side), 152 nets.

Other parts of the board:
C1#2, C2#2: 100uF; CP_Radial_D6.3mm_P2.50mm
C11#2, C12#2: 100uF; CP_Elec_6.3x7.7

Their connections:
+5V: C1#2.1, C2#2.1, C11#2.1, C12#2.1; also elsewhere on the board
GND: C1#2.2, C2#2.2, C11#2.2, C12#2.2; also elsewhere on the board

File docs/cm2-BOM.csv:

Source:,/home/jtf/gith/cm2/pcb/cm2.kicad_sch,,,,,
Date:,Mon 24 Jan 2022 01:46:10 PM PST,,,,,
Tool:,Eeschema 6.0.1-79c1e3a40b~116~ubuntu20.04.1,,,,,
Generator:,/usr/share/kicad/plugins/bom_csv_grouped_by_value_with_fp.py,,,,,
Component Count:,614,,,,,
Ref,Qnty,Value,Cmp name,Footprint,Description,Vendor
"C1, C2, ",2,100uF,C_Polarized_Small_US,Capacitor_THT:CP_Radial_D6.3mm_P2.50mm,"Polarized capacitor, small US symbol",
"C3, C4, C5, C6, C7, C8, C9, C10, ",8,10uF,C_Small,Capacitor_SMD:C_1206_3216Metric_Pad1.33x1.80mm_HandSolder,"Unpolarized capacitor, small symbol",
"C11, C12, ",2,100uF,C_Polarized_Small_US,Capacitor_SMD:CP_Elec_6.3x7.7,"Polarized capacitor, small US symbol",
D00A1 – D31H2,512,LED_Small_ALT,LED_Small_Filled,LED_THT:LED_D5.0mm,"Light emitting diode, small symbol, filled shape",
"H2, H8, H9, H10, ",4,RPi MountingHole,MountingHole,MountingHole:MountingHole_2.5mm,Mounting Hole without connection,
"J1, ",1,top left,Conn_02x06_Odd_Even,Connector_PinHeader_2.54mm:PinHeader_2x06_P2.54mm_Horizontal,"Generic connector, double row, 02x06, odd/even pin numbering scheme (row 1 odd numbers, row 2 even numbers), script generated (kicad-library-utils/schlib/autogen/connector/)",
"J2, ",1,bottom left,Conn_02x06_Odd_Even,Connector_PinSocket_2.54mm:PinSocket_2x06_P2.54mm_Horizontal,"Generic connector, double row, 02x06, odd/even pin numbering scheme (row 1 odd numbers, row 2 even numbers), script generated (kicad-library-utils/schlib/autogen/connector/)",
"J3, ",1,Raspberry_Pi_2_3,Raspberry_Pi_2_3,Connector_PinSocket_2.54mm:PinSocket_2x20_P2.54mm_Vertical,expansion header for Raspberry Pi 2 & 3,
"J4, J5, ",2,Screw_Terminal_01x02,Screw_Terminal_01x02,TerminalBlock:TerminalBlock_bornier-2_P5.08mm,"Generic screw terminal, single row, 01x02, script generated (kicad-library-utils/schlib/autogen/connector/)",
"R1, - R64, ",64,R33,R_US,Resistor_SMD:R_0603_1608Metric_Pad0.98x0.95mm_HandSolder,"Resistor, US symbol",
"U1, U2, ",2,HT1632C-52LQFP,HT1632C-52LQFP,Package_QFP:LQFP-52_14x14mm_P1mm,"LED Matrix Driver, 32×8 or 24×16, 52-LQFP",

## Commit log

2021-05-11 first add
2021-05-12 added python script for pcb array
2021-05-12 checkpoint
2021-05-17 add rpi software
2021-05-19 made simulator and directory
2021-07-28 continue wiring -- 3hr
2021-08-07 wiring, mpunting holes, 3h
2021-08-18 new sw directory
2021-08-24 test 4 CE lines
2021-08-24 get rpi dimensions exact, rerout chip selects, 2 hrs
2021-08-31 Final board check, tape out, and submit. 3hrs
2021-10-05 works on 32x32
2021-11-03 update server for 32 x 32 display
2021-11-09 calculate fps timing in testpatter.py and curltest32.sh
2021-11-09 add python server test
2021-11-09 Add brightness test and frame timing benchmarks
2021-11-12 add hexframe method to send hex frame data
2021-11-12 speed up with sendframe
2021-11-13 different libs for servertest
2021-11-13 add osc server and client
2021-11-24 updates for Zero2, remove unused rotenc
2021-12-01 added CAD files
2022-01-11 update for Kicad version 6
2022-01-24 reorg file tree
2022-01-24 fix errors from v6 conversion
2022-01-24 added BOM files
2022-01-26 added more docs
